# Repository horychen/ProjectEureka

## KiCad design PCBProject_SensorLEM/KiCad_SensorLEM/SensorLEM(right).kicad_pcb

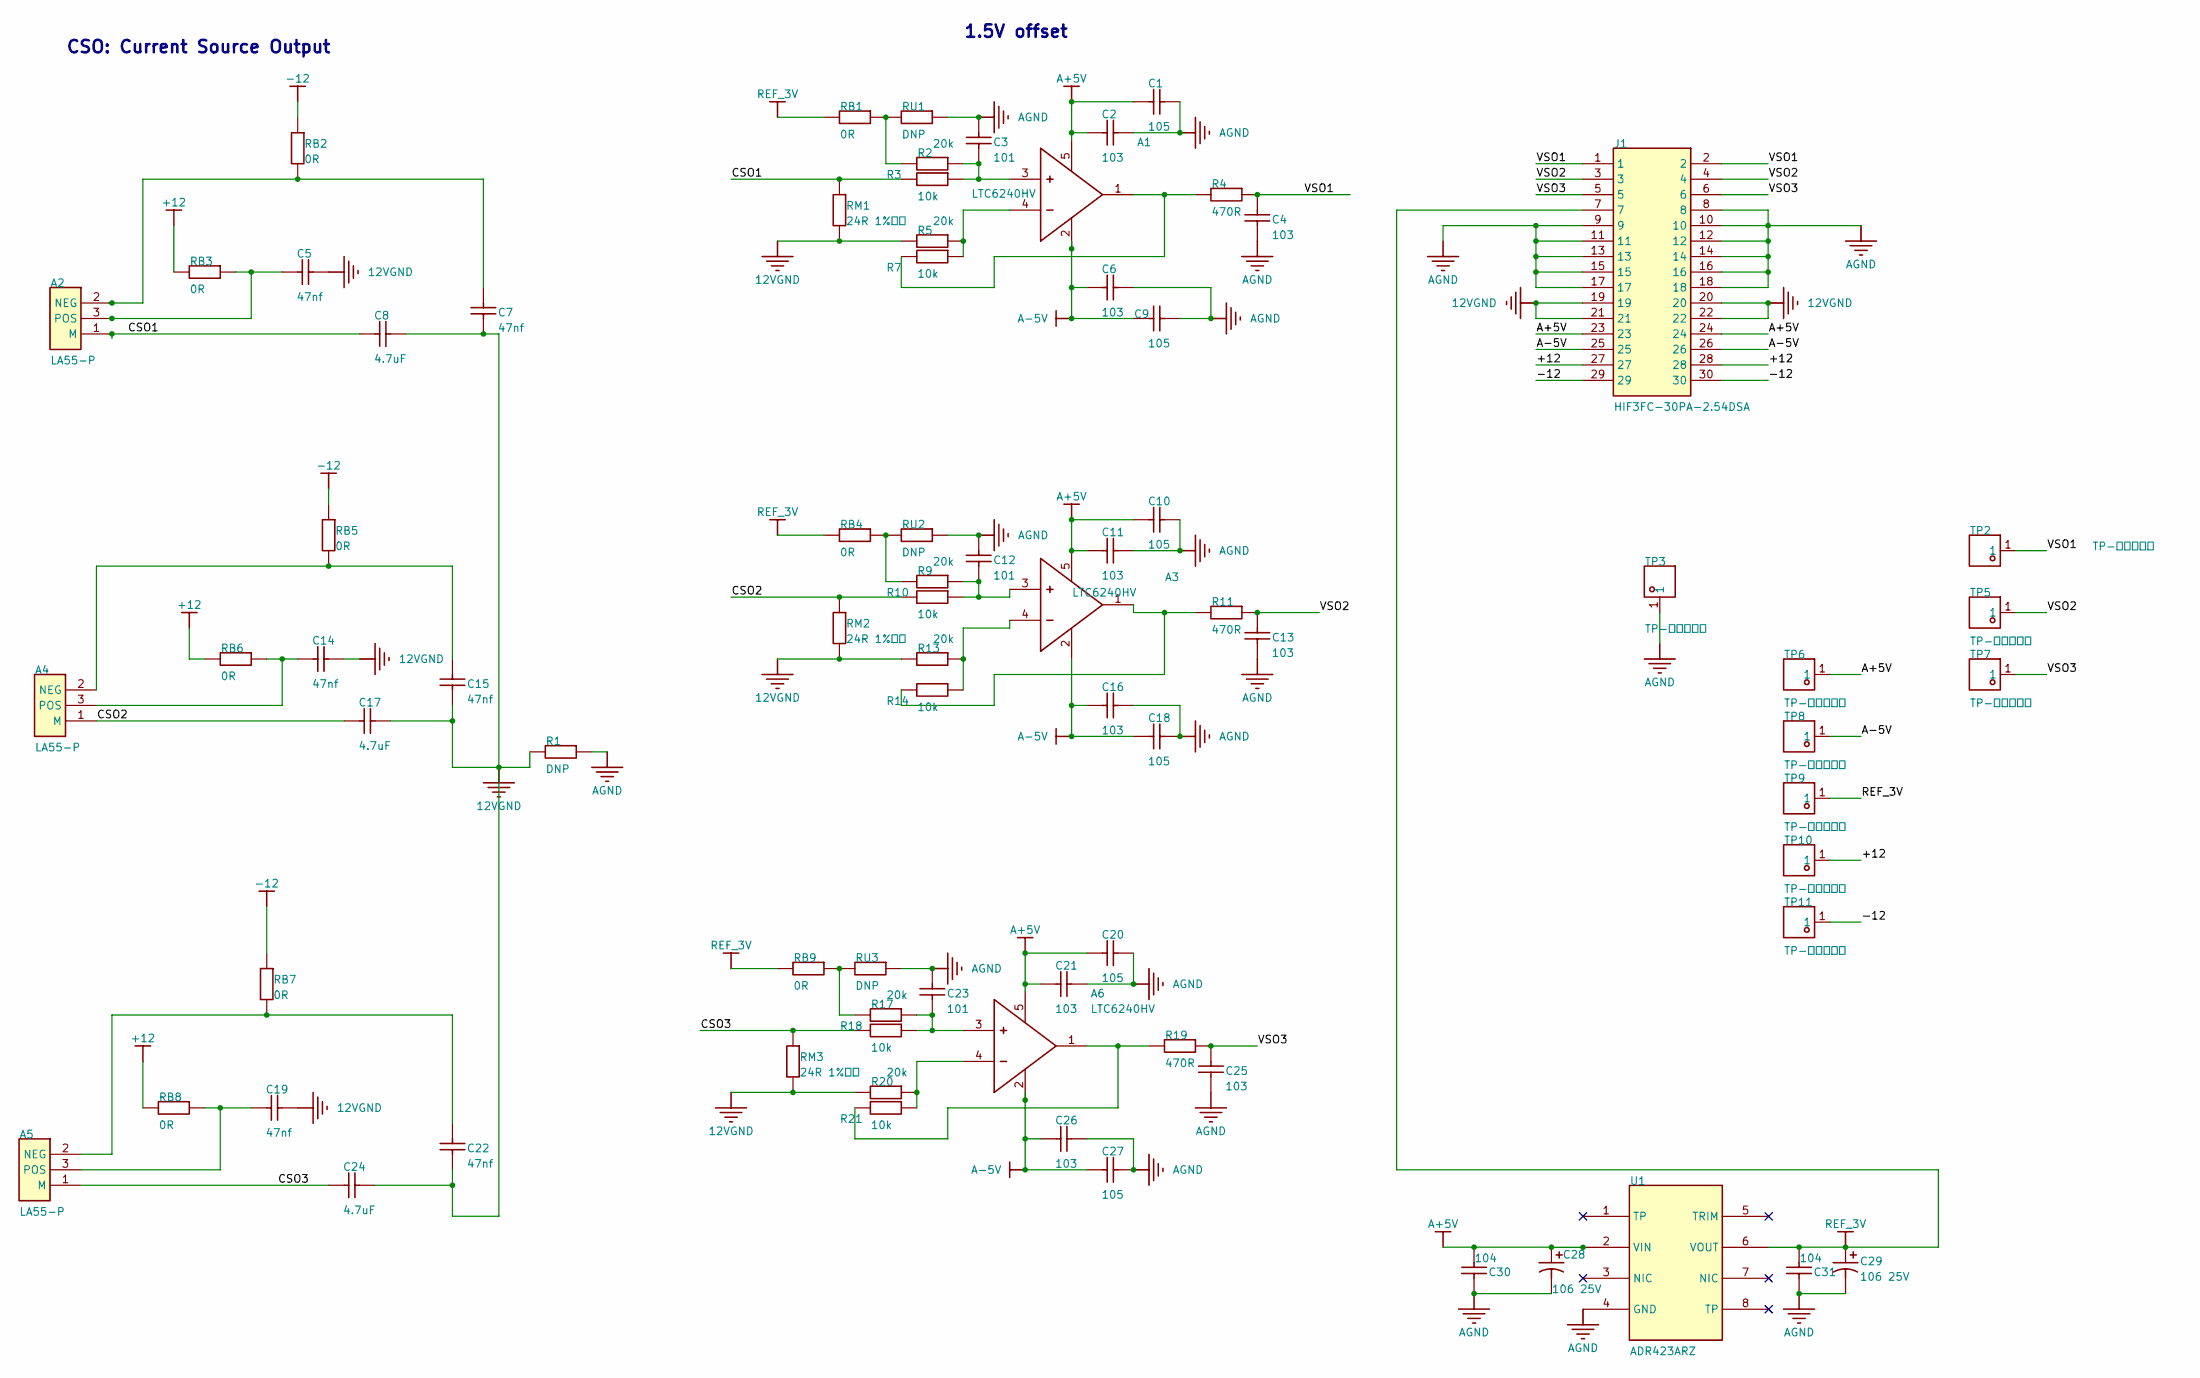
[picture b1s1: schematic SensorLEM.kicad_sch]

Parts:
A1, A3, A6: LTC6240HV; SOT95P280X100-5N; FARNELL # 2294747
A2, A4, A5: LA55-P; XDCR_LA55-P
C1, C9, C10, C18, C20, C27: 105; C_0805_2012Metric
C2, C4, C6, C11, C13, C16, C21, C25, C26: 103; C_0805_2012Metric
C3, C12, C23: 101; C_0805_2012Metric
C5, C7, C14, C15, C19, C22: 47nf; C_0805_2012Metric
C8, C17, C24: 4.7uF; C_0805_2012Metric
C28, C29: 106 25V; 1206 (钽电容)
C30, C31: 104; C_0805_2012Metric
J1: HIF3FC-30PA-2.54DSA; SHDR30W50P254_2X15_4560X850X1200P; MANUFACTURER_PART_NUMBER HIF3FC-30PA-2.54DSA(71); MOUSER PART NUMBER 798-HIF3FC30PA254D71
R1: DNP; R_0805_2012Metric
R2, R5, R9, R13, R17, R20: 20k; R_0805_2012Metric
R3, R7, R10, R14, R18, R21: 10k; R_0805_2012Metric
R4, R11, R19: 470R; R_0805_2012Metric
RB1, RB2, RB3, RB4, RB5, RB6, RB7, RB8, RB9: 0R; R_0805_2012Metric
RM1, RM2, RM3: 24R 1%精度; 2512
RU1, RU2, RU3: DNP; 0805
TP2, TP3, TP5, TP6, TP7, TP8, TP9, TP10, TP11: TP-黄色测试点; TestPoint_THTPad_D2.0mm_Drill1.0mm; MANUFACTURER PART TP-黄色测试点; LCSC PART NAME TP-黄色测试点
U1: ADR423ARZ; SOIC-8; MANUFACTURER_PART_NUMBER ADR423ARZ

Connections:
12VGND: C5.1, C7.2, C8.2, C14.1, C15.2, C17.2, C19.1, C22.2, C24.2, J1.19, J1.20, J1.21, J1.22, R1.2, R5.1, R13.1, R20.1, RM1.2, RM2.2, RM3.2
+12: J1.27, J1.28, RB3.1, RB6.1, RB8.1, TP10.1
-12: J1.29, J1.30, RB2.2, RB5.2, RB7.2, TP11.1
/CSO1: A2.1 (M), C8.1, R3.1, RM1.1
/CSO2: A4.1 (M), C17.1, R10.1, RM2.1
/CSO3: A5.1 (M), C24.1, R18.1, RM3.1
/VSO1: C4.2, J1.1, J1.2, R4.1, TP2.1
/VSO2: C13.2, J1.3, J1.4, R11.1, TP5.1
/VSO3: C25.2, J1.5, J1.6, R19.1, TP7.1
A+5V: A1.5 (Vcc), A3.5 (Vcc), A6.5 (Vcc), C1.2, C2.2, C10.2, C11.2, C20.2, C21.2, C28.1, C30.2, J1.23, J1.24, TP6.1, U1.2 (VIN)
A-5V: A1.2 (Vee), A3.2 (Vee), A6.2 (Vee), C6.2, C9.2, C16.2, C18.2, C26.2, C27.2, J1.25, J1.26, TP8.1
AGND: C1.1, C2.1, C3.2, C4.1, C6.1, C9.1, C10.1, C11.1, C12.2, C13.1, C16.1, C18.1, C20.1, C21.1, C23.2, C25.1, C26.1, C27.1, C28.2, C29.2, C30.1, C31.1, J1.8, J1.9, J1.10, J1.11, J1.12, J1.13, J1.14, J1.15, J1.16, J1.17, J1.18, R1.1, RU1.2, RU2.2, RU3.2, TP3.1, U1.4 (GND)
unnamed: A1.3 (+IN), C3.1, R2.2, R3.2
unnamed: A1.4 (-IN), R5.2, R7.2
unnamed: A1.1 (out), R4.2, R7.1
unnamed: A2.2 (NEG), C7.1, RB2.1
unnamed: A2.3 (POS), C5.2, RB3.2
unnamed: A3.3 (+IN), C12.1, R9.2, R10.2
unnamed: A3.4 (-IN), R13.2, R14.2
unnamed: A3.1 (out), R11.2, R14.1
unnamed: A4.2 (NEG), C15.1, RB5.1
unnamed: A4.3 (POS), C14.2, RB6.2
unnamed: A5.2 (NEG), C22.1, RB7.1
unnamed: A5.3 (POS), C19.2, RB8.2
unnamed: A6.3 (+IN), C23.1, R17.2, R18.2
unnamed: A6.4 (-IN), R20.2, R21.2
unnamed: A6.1 (out), R19.2, R21.1
unnamed: R2.1, RB1.2, RU1.1
unnamed: R9.1, RB4.2, RU2.1
unnamed: R17.1, RB9.2, RU3.1
REF_3V: C29.1, C31.2, J1.7, RB1.1, RB4.1, RB9.1, TP9.1, U1.6 (VOUT)

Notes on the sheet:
1.5V offset
CSO: Current Source Output

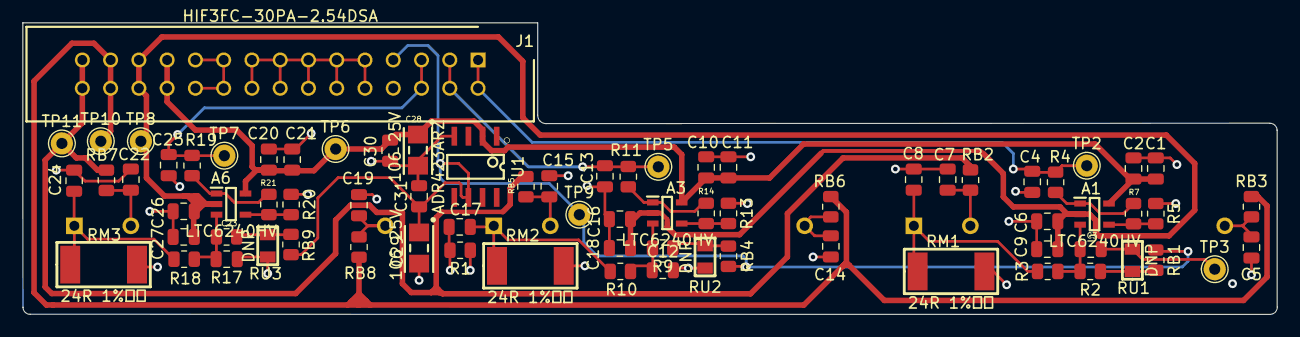
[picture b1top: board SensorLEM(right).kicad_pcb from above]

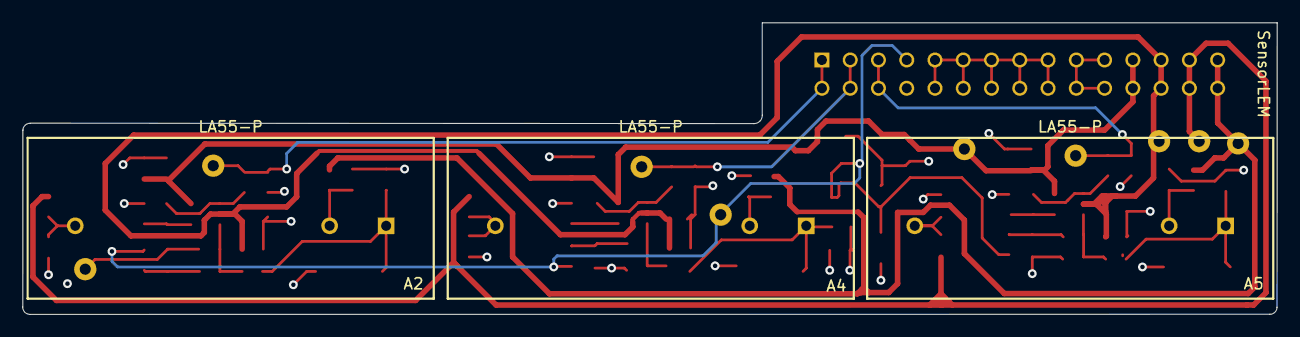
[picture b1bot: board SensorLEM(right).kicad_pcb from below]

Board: 4 copper layers, 112.7 x 26.2 mm, 79 parts (3 on the bottom side), 31 nets.

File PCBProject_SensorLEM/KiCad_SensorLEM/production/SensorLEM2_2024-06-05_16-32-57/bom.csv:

Designator,Footprint,Quantity,Value,LCSC Part #
"A1, A3, A6",SOT95P280X100-5N,3,LTC6240HV,
"A2, A4, A5",XDCR_LA55-P,3,LA55-P,
"C1, C10, C18, C20, C27, C9",0805,6,105,
"C11, C13, C16, C2, C21, C25, C26, C4, C6",0805,9,103,
"C12, C23, C3",0805,3,101,
"C14, C15, C19, C22, C5, C7",0805,6,47nf,
"C17, C24, C8",0805,3,4.7uF,
"C28, C29",1206 (钽电容),2,106 25V,
"C30, C31",0805,2,104,
J1,SHDR30W50P254_2X15_4560X850X1200P,1,HIF3FC-30PA-2.54DSA,
"R10, R14, R18, R21, R3, R7",0805,6,10k,
"R11, R19, R4",0805,3,470R,
"R13, R17, R2, R20, R5, R9",0805,6,20k,
"RB1, RB2, RB3, RB4, RB5, RB6, RB7, RB8, RB9",0805,9,0R,
"RM1, RM2, RM3",2512,3,24R 1%精度,
"TP10, TP11, TP2, TP3, TP5, TP6, TP7, TP8, TP9",TestPoint_THTPad_D2.0mm_Drill1.0mm,9,TP-黄色测试点,
U1,SOIC-8,1,ADR423ARZ,
